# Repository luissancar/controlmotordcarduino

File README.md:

# Control motor dc arduino  
- Entrada vcc.
- Entrada señal arduino PWM.
- Conexión motor.
- Salida alimentación arduino.

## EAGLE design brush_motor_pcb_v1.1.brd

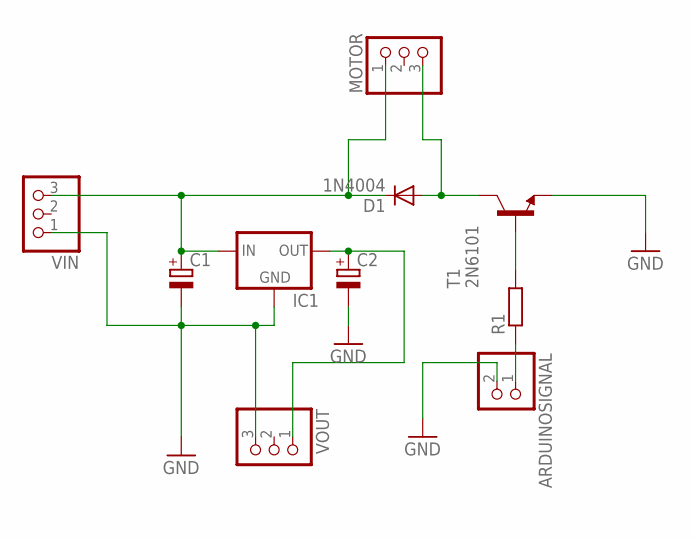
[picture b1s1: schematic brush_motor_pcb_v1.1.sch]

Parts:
ARDUINOSIGNAL: PINHD-1X2; 1X02
C1, C2: CPOL-EUE2.5-6; E2,5-6
D1: 1N4004; DO41-10
IC1: 78XXS
MOTOR: PINHD-1X3; 1X03
R1: R0207/10; 0207/10
T1: 2N6101; TO220
VIN: PINHD-1X3; 1X03
VOUT: PINHD-1X3; 1X03

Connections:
GND: ARDUINOSIGNAL.2, C1.-, C2.-, IC1.GND, T1.3 (E), VIN.1, VOUT.3; also elsewhere on the board
unnamed 1: ARDUINOSIGNAL.1, R1.1; also elsewhere on the board
unnamed: R1.2, T1.1 (B)
unnamed: D1.A, MOTOR.3, T1.2 (C)
unnamed: C1.+, D1.C, IC1.IN, MOTOR.1, VIN.3
unnamed: C2.+, IC1.OUT, VOUT.1

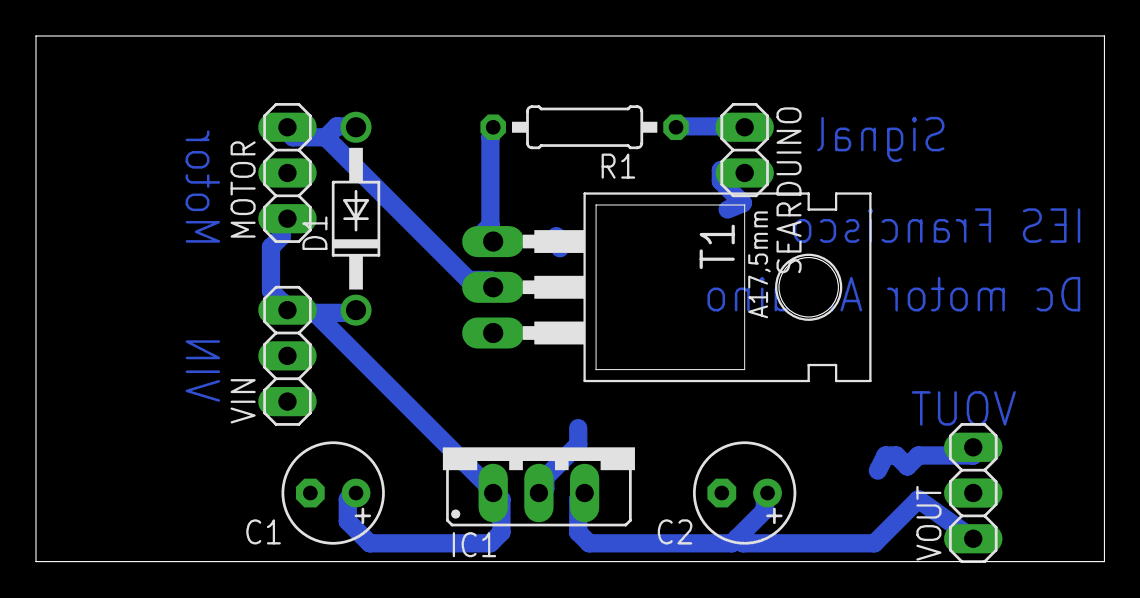
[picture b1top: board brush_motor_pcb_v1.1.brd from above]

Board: 2 copper layers, 59.4 x 29.2 mm, 10 parts (0 on the bottom side), 6 nets.

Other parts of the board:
SEARDUINO: 1X02

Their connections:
GND: SEARDUINO.2; also elsewhere on the board
unnamed 1: SEARDUINO.1; also elsewhere on the board
